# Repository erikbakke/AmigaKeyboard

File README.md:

# AmigaKeyboard
Replacement keyboard supporting MX-compatible switches, for all Amigas except A600 and A1200.

This keyboard design is based around an ATMega32U4 as keyboard controller, and is intended to be used as a replacement keyboards for Amigas with a keyboard controller on the keyboard.  This includes the A500, A1000, A2000, A3000 and A4000, including variants and towers.

The A600 and A1200 have the keyboard controller on the motherboard, and are not compatible with this keyboard design.

There are further notes in the Firmware and PCB folders, relevant to those parts of the project.

It should be noted that this is an early design, but I have built a keyboard up from scratch with this PCB and firmware and it is working on my A4000.
The design is not yet designed to fit into existing Amiga keyboard cases or as a 1:1 replacement for an A500 keyboard.  In order to achieve this, the mounting holes need to be adjusted to fit the external keyboard cases, and most likely a switch mounting plate will also be required.
To avoid disappointment, please keep this in mind before ordering PCBs from this design.

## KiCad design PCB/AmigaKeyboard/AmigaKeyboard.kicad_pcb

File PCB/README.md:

# AmigaKeyboard PCB files

This folder contains the schematics and PCB design for revision 0.2 of the Amiga replacement keyboard design as a KiCad project.  This was initially developed in KiCad 6, and is currently maintained in KiCad 7.

The keyboard works as is with my A4000, but I have not yet had a chance to test it with my A500.  The design should be electrically compatible, and I'm hoping it would be dimensionally compatible as well.
Some work will be required to fit the PCB to existing Amiga external keyboard housings.  The current design has mounting holes to fit a keyboard case I had lying around, so I would be very happy to receive positions and dimensions for mounting holes on the different Amiga keyboards for A2000, A3000 and A4000 models, and will update the design in any way I can to increase compatibility.

I am getting PCBs manufactured from time to time and still have some revision 0.1 PCBs left if anyone want one for experimenting.

## Change log
Revision 0.1:
- Initial PCB version for prototype board manufacture.
  
Revision 0.2:
- A missing trace between D180 and MX80 (numeric pad "4") has been fixed.  The bodge wire fix is no longer needed on revision 0.2.
- Added AVR ISP connector to assist in firmware upgrades and troubleshooting.

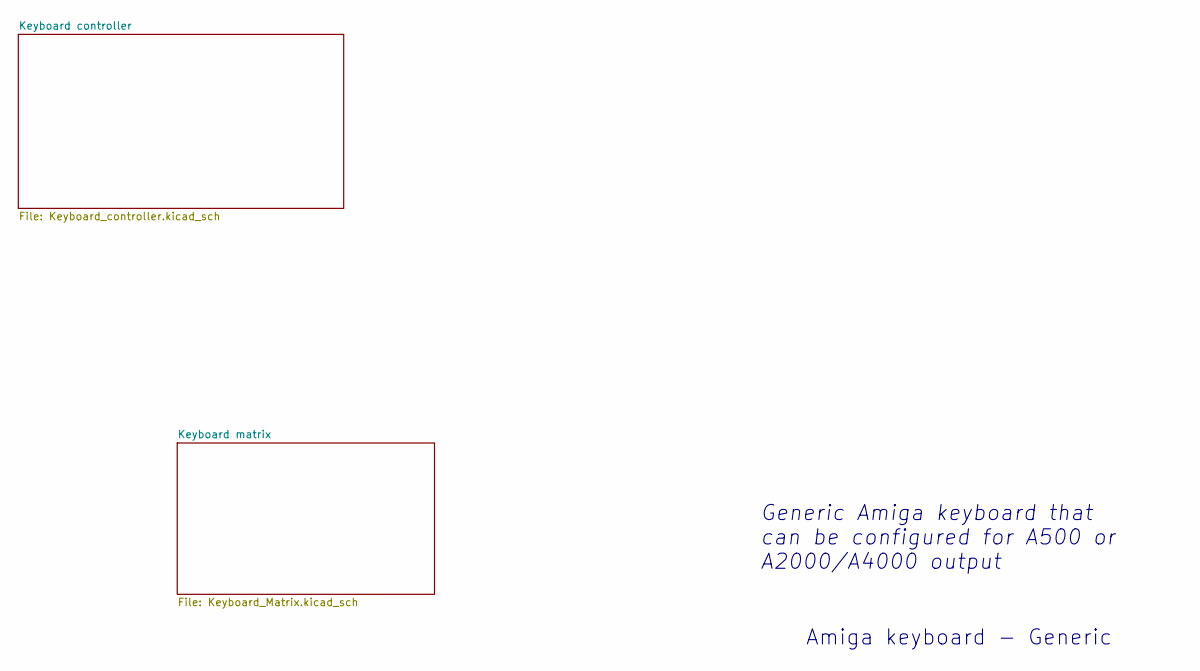
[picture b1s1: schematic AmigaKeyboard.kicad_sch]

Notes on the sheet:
Generic Amiga keyboard that can be configured for A500 or A2000/A4000 output
Amiga keyboard - Generic

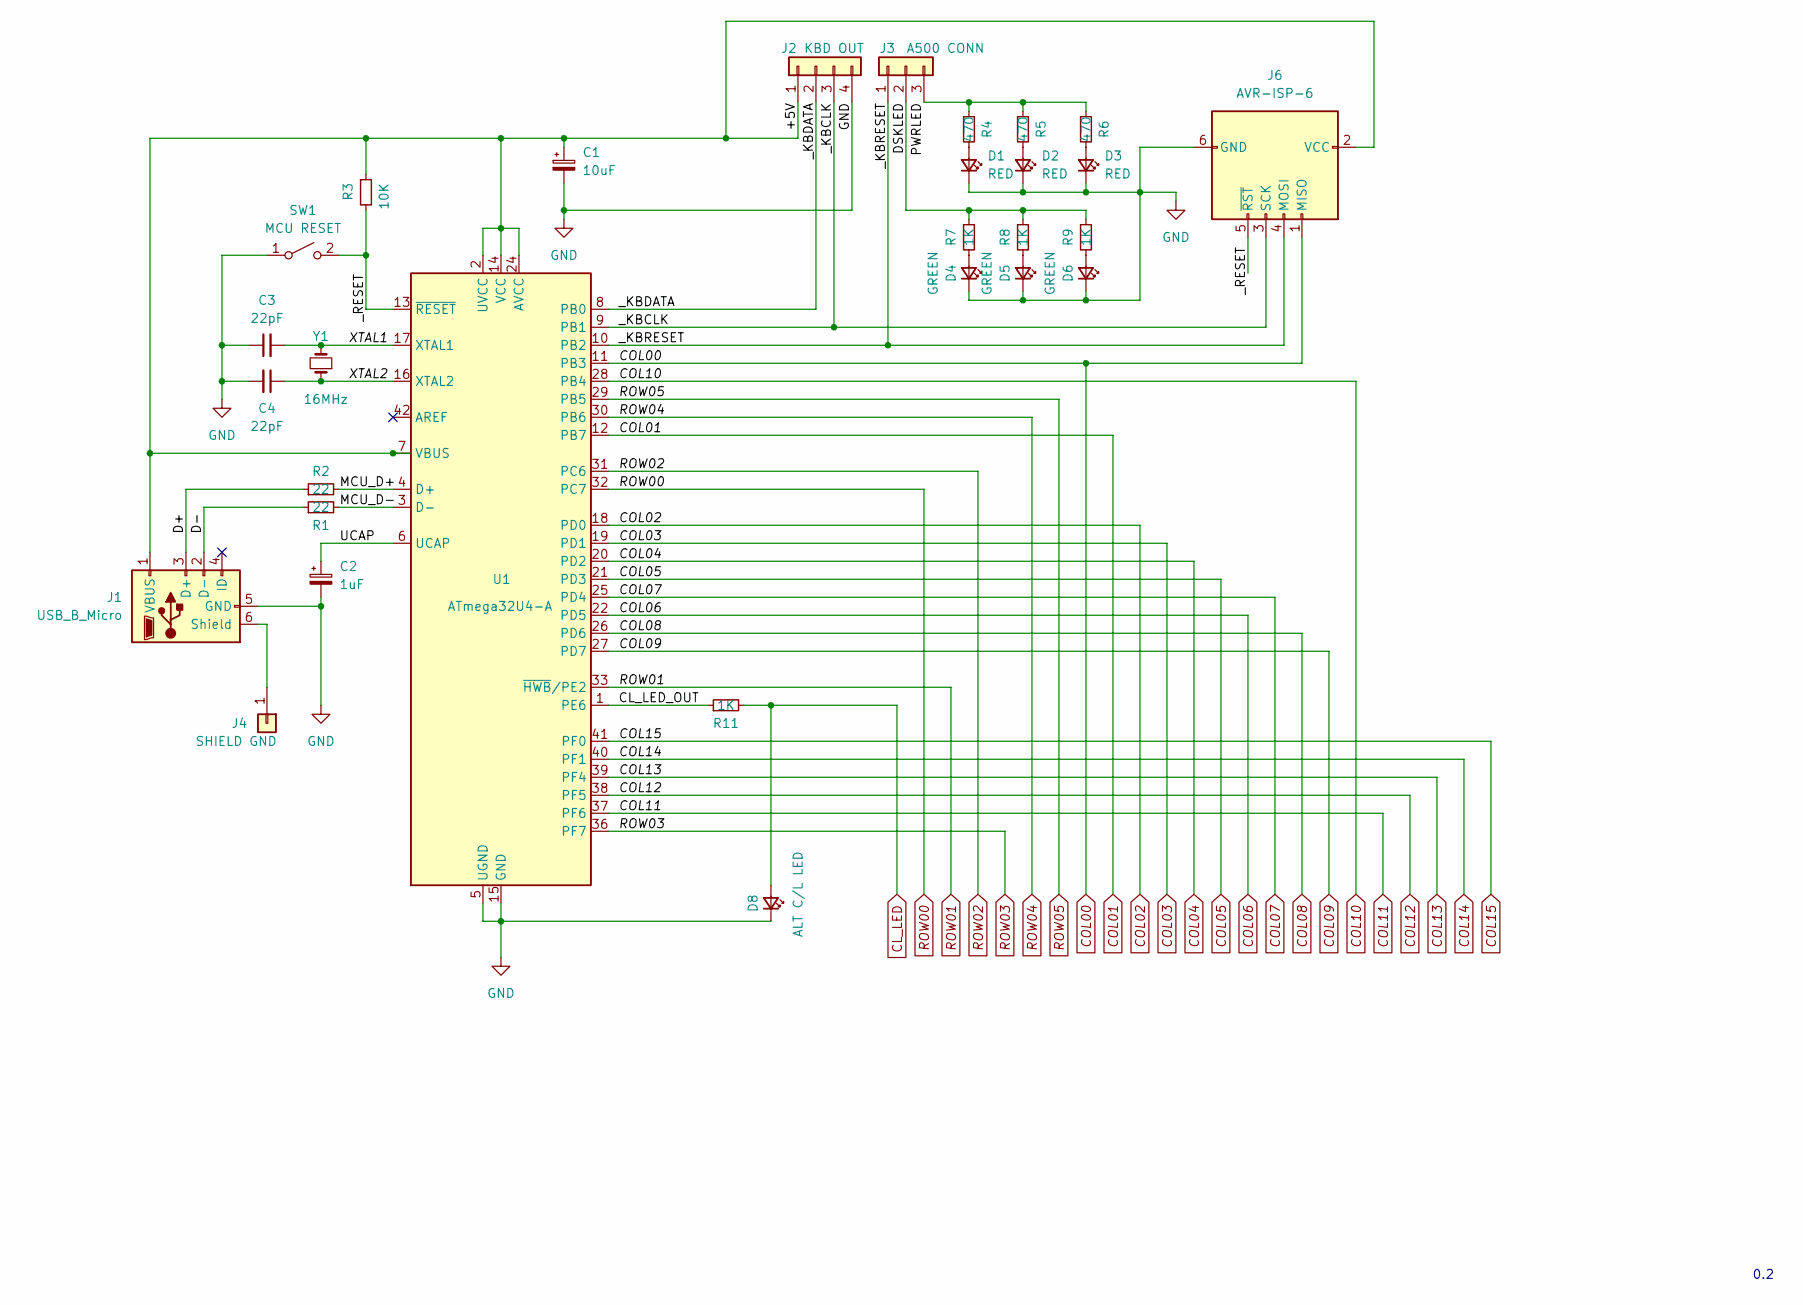
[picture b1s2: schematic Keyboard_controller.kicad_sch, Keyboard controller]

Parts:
C1: 10uF; CP_EIA-7343-31_Kemet-D
C2: 1uF; CP_EIA-3216-18_Kemet-A
C3, C4: 22pF; C_1206_3216Metric
D1, D2, D3: RED; LED_Rectangular_W5.0mm_H2.0mm
D4, D5, D6: GREEN; LED_Rectangular_W5.0mm_H2.0mm
D8: ALT C/L LED; LED_D3.0mm
J1: USB_B_Micro; USB_Micro-B_Wuerth_629105150521_CircularHoles
J2: KBD OUT; SolderWire-0.25sqmm_1x04_P4.2mm_D0.65mm_OD1.7mm
J3: A500 CONN; SolderWire-0.25sqmm_1x03_P4.2mm_D0.65mm_OD1.7mm
J4: SHIELD GND; SolderWire-2.5sqmm_1x01_D2.4mm_OD4.4mm
J6: AVR-ISP-6; PinHeader_2x03_P2.54mm_Vertical
R1, R2: 22; R_1206_3216Metric
R3: 10K; R_1206_3216Metric
R4, R5, R6: 470; R_1206_3216Metric
R7, R8, R9, R11: 1K; R_1206_3216Metric
SW1: MCU RESET; SW_PUSH_6mm
U1: ATmega32U4-A; TQFP-44_10x10mm_P0.8mm
Y1: 16MHz; Crystal_HC49-U_Vertical

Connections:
/Keyboard controller/+5V: C1.1, J1.1 (VBUS), J2.1, J6.2 (VCC), R3.1, U1.2 (UVCC), U1.7 (VBUS), U1.14 (VCC), U1.24 (AVCC), U1.34 (VCC), U1.44 (AVCC)
/Keyboard controller/CL_LED_OUT: R11.1, U1.1 (PE6)
/Keyboard controller/D+: J1.3 (D+), R2.1
/Keyboard controller/D-: J1.2 (D-), R1.1
/Keyboard controller/DSKLED: J3.2, R7.1, R8.1, R9.1
/Keyboard controller/MCU_D+: R2.2, U1.4 (D+)
/Keyboard controller/MCU_D-: R1.2, U1.3 (D-)
/Keyboard controller/PWRLED: J3.3, R4.1, R5.1, R6.1
/Keyboard controller/UCAP: C2.1, U1.6 (UCAP)
/Keyboard controller/XTAL1: C3.2, U1.17 (XTAL1), Y1.2
/Keyboard controller/XTAL2: C4.1, U1.16 (XTAL2), Y1.1
/Keyboard controller/_KBCLK: J2.3, J6.3 (SCK), U1.9 (PB1)
/Keyboard controller/_KBDATA: J2.2, U1.8 (PB0)
/Keyboard controller/_KBRESET: J3.1, J6.4 (MOSI), U1.10 (PB2)
/Keyboard controller/_RESET: J6.5 (~RST), R3.2, SW1.2 (B), U1.13 (~RESET)
CL_LED: D8.2 (A), R11.2; also elsewhere on the board
COL00: J6.1 (MISO), U1.11 (PB3); also elsewhere on the board
COL01: U1.12 (PB7); also elsewhere on the board
COL02: U1.18 (PD0); also elsewhere on the board
COL03: U1.19 (PD1); also elsewhere on the board
COL04: U1.20 (PD2); also elsewhere on the board
COL05: U1.21 (PD3); also elsewhere on the board
COL06: U1.22 (PD5); also elsewhere on the board
COL07: U1.25 (PD4); also elsewhere on the board
COL08: U1.26 (PD6); also elsewhere on the board
COL09: U1.27 (PD7); also elsewhere on the board
COL10: U1.28 (PB4); also elsewhere on the board
COL11: U1.37 (PF6); also elsewhere on the board
COL12: U1.38 (PF5); also elsewhere on the board
COL13: U1.39 (PF4); also elsewhere on the board
COL14: U1.40 (PF1); also elsewhere on the board
COL15: U1.41 (PF0); also elsewhere on the board
GND: C1.2, C2.2, C3.1, C4.2, D1.1 (K), D2.1 (K), D3.1 (K), D4.1 (K), D5.1 (K), D6.1 (K), D8.1 (K), J1.5 (GND), J2.4, J6.6 (GND), SW1.1 (A), U1.5 (UGND), U1.15 (GND), U1.23 (GND), U1.35 (GND), U1.43 (GND); also elsewhere on the board
unnamed: D1.2 (A), R4.2
unnamed: D2.2 (A), R5.2
unnamed: D3.2 (A), R6.2
unnamed: D4.2 (A), R7.2
unnamed: D5.2 (A), R8.2
unnamed: D6.2 (A), R9.2
unnamed: J1.6 (Shield), J4.1
ROW00: U1.32 (PC7); also elsewhere on the board
ROW01: U1.33 (~HWB/PE2); also elsewhere on the board
ROW02: U1.31 (PC6); also elsewhere on the board
ROW03: U1.36 (PF7); also elsewhere on the board
ROW04: U1.30 (PB6); also elsewhere on the board
ROW05: U1.29 (PB5); also elsewhere on the board

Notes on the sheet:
0.2

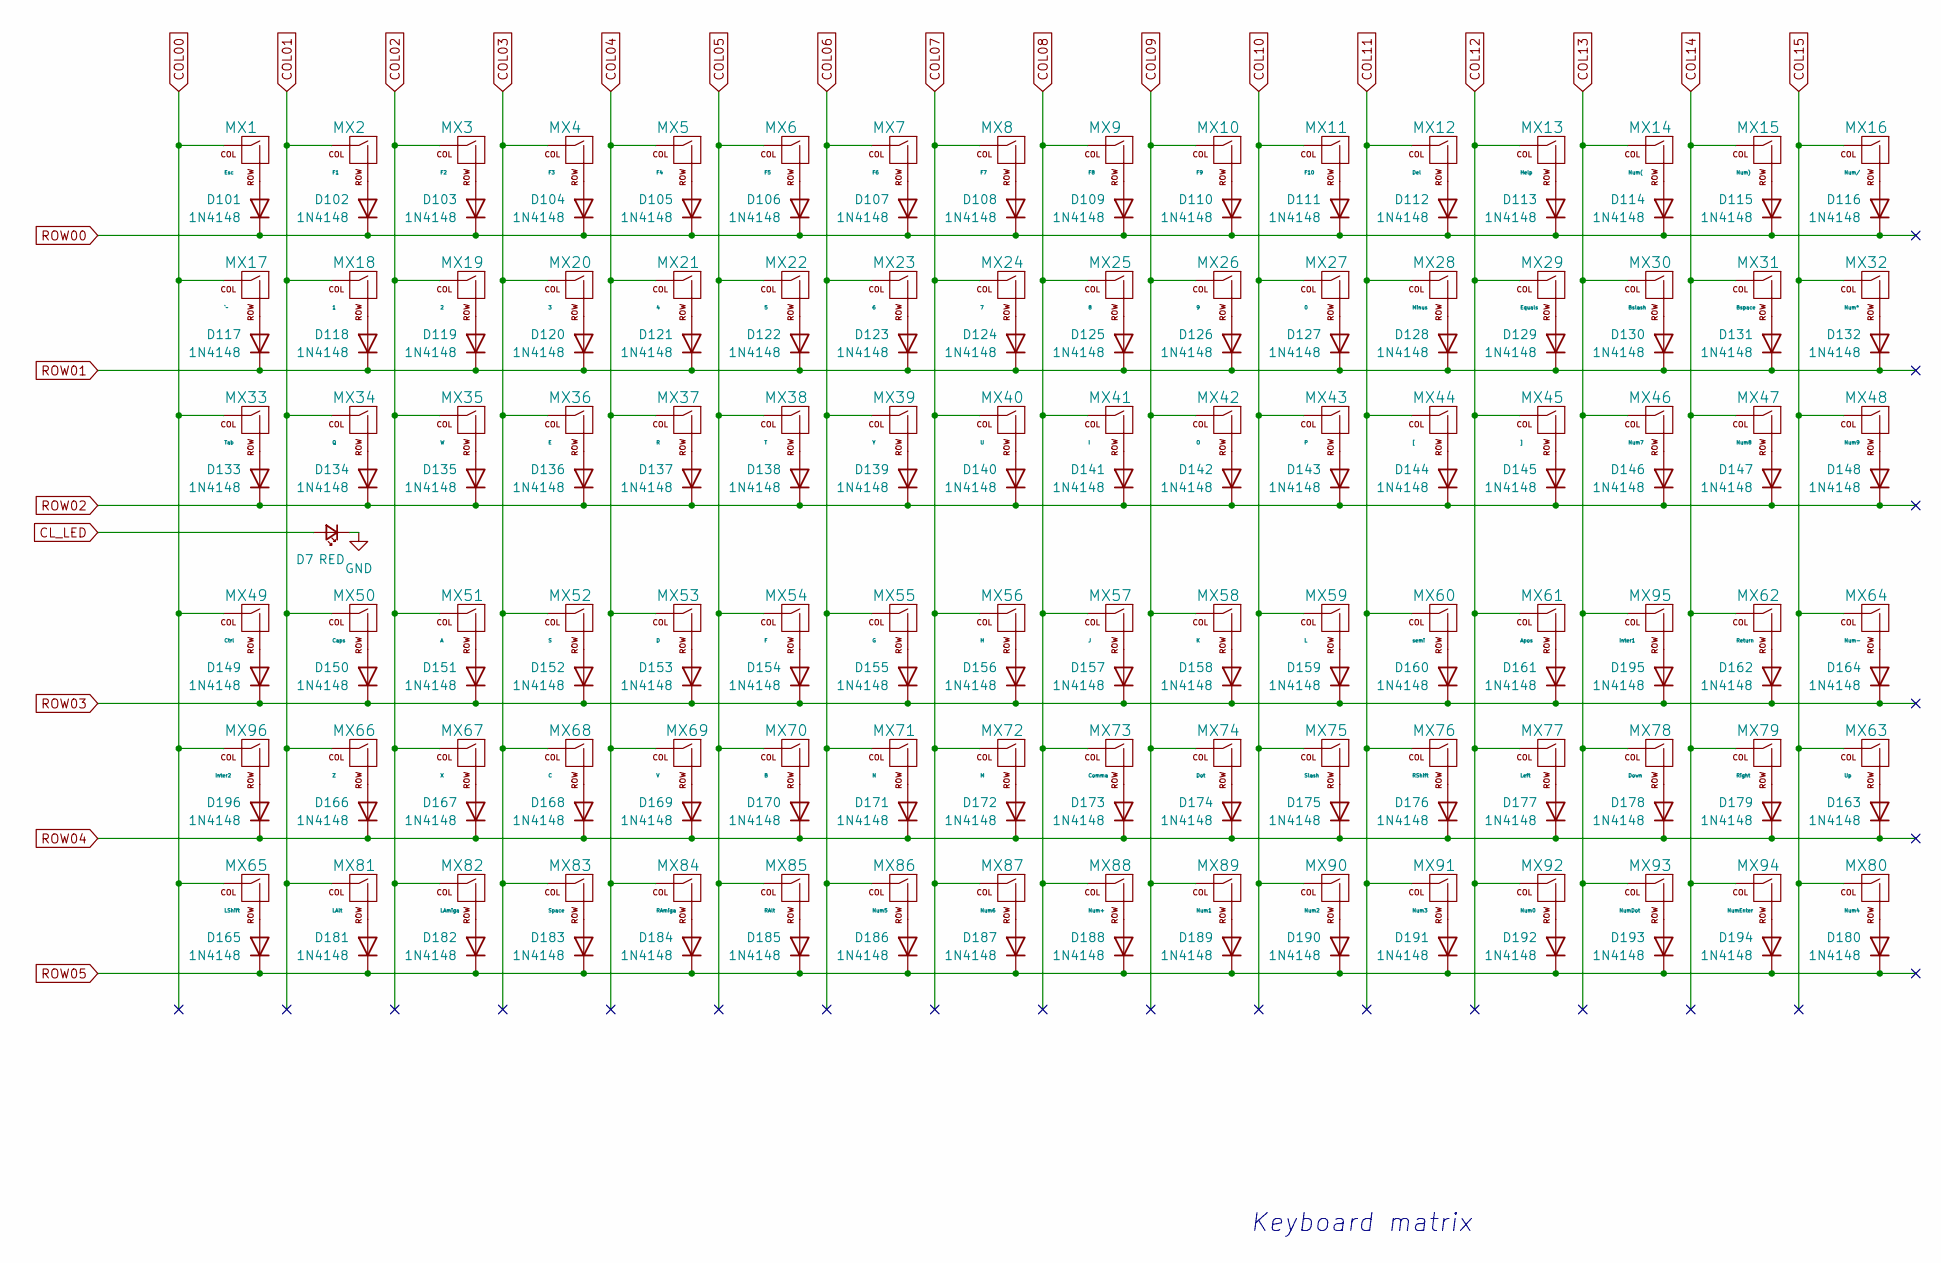
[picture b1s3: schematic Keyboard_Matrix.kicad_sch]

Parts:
D7: RED; LED_0805_2012Metric
D101, D102, D103, D104, D105, D106, D107, D108, D109, D110, D111, D112, D113, D114, D115, D116, D117, D118, D119, D120, D121, D122, D123, D124, D125, D126, D127, D128, D129, D130, D131, D132, D133, D134, D135, D136, D137, D138, D139, D140, D141, D142, D143, D144, D145, D146, D147, D148, D149, D150, D151, D152, D153, D154, D155, D156, D157, D158, D159, D160, D161, D162, D163, D164, D165, D166, D167, D168, D169, D170, D171, D172, D173, D174, D175, D176, D177, D178, D179, D180, D181, D182, D183, D184, D185, D186, D187, D188, D189, D190, D191, D192, D193, D194, D195, D196: 1N4148; D_0805_2012Metric_Pad1.15x1.40mm_HandSolder
MX1: Esc; SW_Cherry_MX_PCB_1.00u
MX2: F1; SW_Cherry_MX_PCB_1.25u
MX3: F2; SW_Cherry_MX_PCB_1.25u
MX4: F3; SW_Cherry_MX_PCB_1.25u
MX5: F4; SW_Cherry_MX_PCB_1.25u
MX6: F5; SW_Cherry_MX_PCB_1.25u
MX7: F6; SW_Cherry_MX_PCB_1.25u
MX8: F7; SW_Cherry_MX_PCB_1.25u
MX9: F8; SW_Cherry_MX_PCB_1.25u
MX10: F9; SW_Cherry_MX_PCB_1.25u
MX11: F10; SW_Cherry_MX_PCB_1.25u
MX12: Del; SW_Cherry_MX_PCB_1.50u
MX13: Help; SW_Cherry_MX_PCB_1.50u
MX14: Num(; SW_Cherry_MX_PCB_1.00u
MX15: Num); SW_Cherry_MX_PCB_1.00u
MX16: Num/; SW_Cherry_MX_PCB_1.00u
MX17: `~; SW_Cherry_MX_PCB_1.50u
MX18: 1; SW_Cherry_MX_PCB_1.00u
MX19: 2; SW_Cherry_MX_PCB_1.00u
MX20: 3; SW_Cherry_MX_PCB_1.00u
MX21: 4; SW_Cherry_MX_PCB_1.00u
MX22: 5; SW_Cherry_MX_PCB_1.00u
MX23: 6; SW_Cherry_MX_PCB_1.00u
MX24: 7; SW_Cherry_MX_PCB_1.00u
MX25: 8; SW_Cherry_MX_PCB_1.00u
MX26: 9; SW_Cherry_MX_PCB_1.00u
MX27: 0; SW_Cherry_MX_PCB_1.00u
MX28: Minus; SW_Cherry_MX_PCB_1.00u
MX29: Equals; SW_Cherry_MX_PCB_1.00u
MX30: Bslash; SW_Cherry_MX_PCB_1.00u
MX31: Bspace; SW_Cherry_MX_PCB_1.00u
MX32: Num*; SW_Cherry_MX_PCB_1.00u
MX33: Tab; SW_Cherry_MX_PCB_2.00u
MX34: Q; SW_Cherry_MX_PCB_1.00u
MX35: W; SW_Cherry_MX_PCB_1.00u
MX36: E; SW_Cherry_MX_PCB_1.00u
MX37: R; SW_Cherry_MX_PCB_1.00u
MX38: T; SW_Cherry_MX_PCB_1.00u
MX39: Y; SW_Cherry_MX_PCB_1.00u
MX40: U; SW_Cherry_MX_PCB_1.00u
MX41: I; SW_Cherry_MX_PCB_1.00u
MX42: O; SW_Cherry_MX_PCB_1.00u
MX43: P; SW_Cherry_MX_PCB_1.00u
MX44: [; SW_Cherry_MX_PCB_1.00u
MX45: ]; SW_Cherry_MX_PCB_1.00u
MX46: Num7; SW_Cherry_MX_PCB_1.00u
MX47: Num8; SW_Cherry_MX_PCB_1.00u
MX48: Num9; SW_Cherry_MX_PCB_1.00u
MX49: Ctrl; SW_Cherry_MX_PCB_1.25u
MX50: Caps; SW_Cherry_MX_PCB_1.00u
MX51: A; SW_Cherry_MX_PCB_1.00u
MX52: S; SW_Cherry_MX_PCB_1.00u
MX53: D; SW_Cherry_MX_PCB_1.00u
MX54: F; SW_Cherry_MX_PCB_1.00u
MX55: G; SW_Cherry_MX_PCB_1.00u
MX56: H; SW_Cherry_MX_PCB_1.00u
MX57: J; SW_Cherry_MX_PCB_1.00u
MX58: K; SW_Cherry_MX_PCB_1.00u
MX59: L; SW_Cherry_MX_PCB_1.00u
MX60: semi; SW_Cherry_MX_PCB_1.00u
MX61: Apos; SW_Cherry_MX_PCB_1.00u
MX62: Return; SW_Cherry_MX_PCB_ISOEnter
MX63: Up; SW_Cherry_MX_PCB_1.00u
MX64: Num-; SW_Cherry_MX_PCB_1.00u
MX65: LShift; SW_Cherry_MX_PCB_1.75u
MX66: Z; SW_Cherry_MX_PCB_1.00u
MX67: X; SW_Cherry_MX_PCB_1.00u
MX68: C; SW_Cherry_MX_PCB_1.00u
MX69: V; SW_Cherry_MX_PCB_1.00u
MX70: B; SW_Cherry_MX_PCB_1.00u
MX71: N; SW_Cherry_MX_PCB_1.00u
MX72: M; SW_Cherry_MX_PCB_1.00u
MX73: Comma; SW_Cherry_MX_PCB_1.00u
MX74: Dot; SW_Cherry_MX_PCB_1.00u
MX75: Slash; SW_Cherry_MX_PCB_1.00u
MX76: RShift; SW_Cherry_MX_PCB_2.50u
MX77: Left; SW_Cherry_MX_PCB_1.00u
MX78: Down; SW_Cherry_MX_PCB_1.00u
MX79: Right; SW_Cherry_MX_PCB_1.00u
MX80: Num4; SW_Cherry_MX_PCB_1.00u
MX81: LAlt; SW_Cherry_MX_PCB_1.25u
MX82: LAmiga; SW_Cherry_MX_PCB_1.25u
MX83: Space; SW_Cherry_MX_PCB_9.00u
MX84: RAmiga; SW_Cherry_MX_PCB_1.25u
MX85: RAlt; SW_Cherry_MX_PCB_1.25u
MX86: Num5; SW_Cherry_MX_PCB_1.00u
MX87: Num6; SW_Cherry_MX_PCB_1.00u
MX88: Num+; SW_Cherry_MX_PCB_1.00u
MX89: Num1; SW_Cherry_MX_PCB_1.00u
MX90: Num2; SW_Cherry_MX_PCB_1.00u
MX91: Num3; SW_Cherry_MX_PCB_1.00u
MX92: Num0; SW_Cherry_MX_PCB_2.00u
MX93: NumDot; SW_Cherry_MX_PCB_1.00u
MX94: NumEnter; SW_Cherry_MX_PCB_2.00u_90deg
MX95: Inter1; SW_Cherry_MX_PCB_1.00u
MX96: Inter2; SW_Cherry_MX_PCB_1.00u

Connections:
CL_LED: D7.2 (A); also elsewhere on the board
COL00: MX1.1 (COL), MX17.1 (COL), MX33.1 (COL), MX49.1 (COL), MX65.1 (COL), MX96.1 (COL); also elsewhere on the board
COL01: MX2.1 (COL), MX18.1 (COL), MX34.1 (COL), MX50.1 (COL), MX66.1 (COL), MX81.1 (COL); also elsewhere on the board
COL02: MX3.1 (COL), MX19.1 (COL), MX35.1 (COL), MX51.1 (COL), MX67.1 (COL), MX82.1 (COL); also elsewhere on the board
COL03: MX4.1 (COL), MX20.1 (COL), MX36.1 (COL), MX52.1 (COL), MX68.1 (COL), MX83.1 (COL); also elsewhere on the board
COL04: MX5.1 (COL), MX21.1 (COL), MX37.1 (COL), MX53.1 (COL), MX69.1 (COL), MX84.1 (COL); also elsewhere on the board
COL05: MX6.1 (COL), MX22.1 (COL), MX38.1 (COL), MX54.1 (COL), MX70.1 (COL), MX85.1 (COL); also elsewhere on the board
COL06: MX7.1 (COL), MX23.1 (COL), MX39.1 (COL), MX55.1 (COL), MX71.1 (COL), MX86.1 (COL); also elsewhere on the board
COL07: MX8.1 (COL), MX24.1 (COL), MX40.1 (COL), MX56.1 (COL), MX72.1 (COL), MX87.1 (COL); also elsewhere on the board
COL08: MX9.1 (COL), MX25.1 (COL), MX41.1 (COL), MX57.1 (COL), MX73.1 (COL), MX88.1 (COL); also elsewhere on the board
COL09: MX10.1 (COL), MX26.1 (COL), MX42.1 (COL), MX58.1 (COL), MX74.1 (COL), MX89.1 (COL); also elsewhere on the board
COL10: MX11.1 (COL), MX27.1 (COL), MX43.1 (COL), MX59.1 (COL), MX75.1 (COL), MX90.1 (COL); also elsewhere on the board
COL11: MX12.1 (COL), MX28.1 (COL), MX44.1 (COL), MX60.1 (COL), MX76.1 (COL), MX91.1 (COL); also elsewhere on the board
COL12: MX13.1 (COL), MX29.1 (COL), MX45.1 (COL), MX61.1 (COL), MX77.1 (COL), MX92.1 (COL); also elsewhere on the board
COL13: MX14.1 (COL), MX30.1 (COL), MX46.1 (COL), MX78.1 (COL), MX93.1 (COL), MX95.1 (COL); also elsewhere on the board
COL14: MX15.1 (COL), MX31.1 (COL), MX47.1 (COL), MX62.1 (COL), MX79.1 (COL), MX94.1 (COL); also elsewhere on the board
COL15: MX16.1 (COL), MX32.1 (COL), MX48.1 (COL), MX63.1 (COL), MX64.1 (COL), MX80.1 (COL); also elsewhere on the board
GND: D7.1 (K); also elsewhere on the board
unnamed: D101.2 (A), MX1.2 (ROW)
unnamed: D102.2 (A), MX2.2 (ROW)
unnamed: D103.2 (A), MX3.2 (ROW)
unnamed: D104.2 (A), MX4.2 (ROW)
unnamed: D105.2 (A), MX5.2 (ROW)
unnamed: D106.2 (A), MX6.2 (ROW)
unnamed: D107.2 (A), MX7.2 (ROW)
unnamed: D108.2 (A), MX8.2 (ROW)
unnamed: D109.2 (A), MX9.2 (ROW)
unnamed: D110.2 (A), MX10.2 (ROW)
unnamed: D111.2 (A), MX11.2 (ROW)
unnamed: D112.2 (A), MX12.2 (ROW)
unnamed: D113.2 (A), MX13.2 (ROW)
unnamed: D114.2 (A), MX14.2 (ROW)
unnamed: D115.2 (A), MX15.2 (ROW)
unnamed: D116.2 (A), MX16.2 (ROW)
unnamed: D117.2 (A), MX17.2 (ROW)
unnamed: D118.2 (A), MX18.2 (ROW)
unnamed: D119.2 (A), MX19.2 (ROW)
unnamed: D120.2 (A), MX20.2 (ROW)
unnamed: D121.2 (A), MX21.2 (ROW)
unnamed: D122.2 (A), MX22.2 (ROW)
unnamed: D123.2 (A), MX23.2 (ROW)
unnamed: D124.2 (A), MX24.2 (ROW)
unnamed: D125.2 (A), MX25.2 (ROW)
unnamed: D126.2 (A), MX26.2 (ROW)
unnamed: D127.2 (A), MX27.2 (ROW)
unnamed: D128.2 (A), MX28.2 (ROW)
unnamed: D129.2 (A), MX29.2 (ROW)
unnamed: D130.2 (A), MX30.2 (ROW)
unnamed: D131.2 (A), MX31.2 (ROW)
unnamed: D132.2 (A), MX32.2 (ROW)
unnamed: D133.2 (A), MX33.2 (ROW)
unnamed: D134.2 (A), MX34.2 (ROW)
unnamed: D135.2 (A), MX35.2 (ROW)
unnamed: D136.2 (A), MX36.2 (ROW)
unnamed: D137.2 (A), MX37.2 (ROW)
unnamed: D138.2 (A), MX38.2 (ROW)
unnamed: D139.2 (A), MX39.2 (ROW)
unnamed: D140.2 (A), MX40.2 (ROW)
unnamed: D141.2 (A), MX41.2 (ROW)
unnamed: D142.2 (A), MX42.2 (ROW)
unnamed: D143.2 (A), MX43.2 (ROW)
unnamed: D144.2 (A), MX44.2 (ROW)
unnamed: D145.2 (A), MX45.2 (ROW)
unnamed: D146.2 (A), MX46.2 (ROW)
unnamed: D147.2 (A), MX47.2 (ROW)
unnamed: D148.2 (A), MX48.2 (ROW)
unnamed: D149.2 (A), MX49.2 (ROW)
unnamed: D150.2 (A), MX50.2 (ROW)
unnamed: D151.2 (A), MX51.2 (ROW)
unnamed: D152.2 (A), MX52.2 (ROW)
unnamed: D153.2 (A), MX53.2 (ROW)
unnamed: D154.2 (A), MX54.2 (ROW)
unnamed: D155.2 (A), MX55.2 (ROW)
unnamed: D156.2 (A), MX56.2 (ROW)
unnamed: D157.2 (A), MX57.2 (ROW)
unnamed: D158.2 (A), MX58.2 (ROW)
unnamed: D159.2 (A), MX59.2 (ROW)
unnamed: D160.2 (A), MX60.2 (ROW)
unnamed: D161.2 (A), MX61.2 (ROW)
unnamed: D162.2 (A), MX62.2 (ROW)
unnamed: D163.2 (A), MX63.2 (ROW)
unnamed: D164.2 (A), MX64.2 (ROW)
unnamed: D165.2 (A), MX65.2 (ROW)
unnamed: D166.2 (A), MX66.2 (ROW)
unnamed: D167.2 (A), MX67.2 (ROW)
unnamed: D168.2 (A), MX68.2 (ROW)
unnamed: D169.2 (A), MX69.2 (ROW)
unnamed: D170.2 (A), MX70.2 (ROW)
unnamed: D171.2 (A), MX71.2 (ROW)
unnamed: D172.2 (A), MX72.2 (ROW)
unnamed: D173.2 (A), MX73.2 (ROW)
unnamed: D174.2 (A), MX74.2 (ROW)
unnamed: D175.2 (A), MX75.2 (ROW)
unnamed: D176.2 (A), MX76.2 (ROW)
unnamed: D177.2 (A), MX77.2 (ROW)
unnamed: D178.2 (A), MX78.2 (ROW)
unnamed: D179.2 (A), MX79.2 (ROW)
unnamed: D180.2 (A), MX80.2 (ROW)
unnamed: D181.2 (A), MX81.2 (ROW)
unnamed: D182.2 (A), MX82.2 (ROW)
unnamed: D183.2 (A), MX83.2 (ROW)
unnamed: D184.2 (A), MX84.2 (ROW)
unnamed: D185.2 (A), MX85.2 (ROW)
unnamed: D186.2 (A), MX86.2 (ROW)
unnamed: D187.2 (A), MX87.2 (ROW)
unnamed: D188.2 (A), MX88.2 (ROW)
unnamed: D189.2 (A), MX89.2 (ROW)
unnamed: D190.2 (A), MX90.2 (ROW)
unnamed: D191.2 (A), MX91.2 (ROW)
unnamed: D192.2 (A), MX92.2 (ROW)
unnamed: D193.2 (A), MX93.2 (ROW)
unnamed: D194.2 (A), MX94.2 (ROW)
unnamed: D195.2 (A), MX95.2 (ROW)
unnamed: D196.2 (A), MX96.2 (ROW)
ROW00: D101.1 (K), D102.1 (K), D103.1 (K), D104.1 (K), D105.1 (K), D106.1 (K), D107.1 (K), D108.1 (K), D109.1 (K), D110.1 (K), D111.1 (K), D112.1 (K), D113.1 (K), D114.1 (K), D115.1 (K), D116.1 (K); also elsewhere on the board
ROW01: D117.1 (K), D118.1 (K), D119.1 (K), D120.1 (K), D121.1 (K), D122.1 (K), D123.1 (K), D124.1 (K), D125.1 (K), D126.1 (K), D127.1 (K), D128.1 (K), D129.1 (K), D130.1 (K), D131.1 (K), D132.1 (K); also elsewhere on the board
ROW02: D133.1 (K), D134.1 (K), D135.1 (K), D136.1 (K), D137.1 (K), D138.1 (K), D139.1 (K), D140.1 (K), D141.1 (K), D142.1 (K), D143.1 (K), D144.1 (K), D145.1 (K), D146.1 (K), D147.1 (K), D148.1 (K); also elsewhere on the board
ROW03: D149.1 (K), D150.1 (K), D151.1 (K), D152.1 (K), D153.1 (K), D154.1 (K), D155.1 (K), D156.1 (K), D157.1 (K), D158.1 (K), D159.1 (K), D160.1 (K), D161.1 (K), D162.1 (K), D164.1 (K), D195.1 (K); also elsewhere on the board
ROW04: D163.1 (K), D166.1 (K), D167.1 (K), D168.1 (K), D169.1 (K), D170.1 (K), D171.1 (K), D172.1 (K), D173.1 (K), D174.1 (K), D175.1 (K), D176.1 (K), D177.1 (K), D178.1 (K), D179.1 (K), D196.1 (K); also elsewhere on the board
ROW05: D165.1 (K), D180.1 (K), D181.1 (K), D182.1 (K), D183.1 (K), D184.1 (K), D185.1 (K), D186.1 (K), D187.1 (K), D188.1 (K), D189.1 (K), D190.1 (K), D191.1 (K), D192.1 (K), D193.1 (K), D194.1 (K); also elsewhere on the board

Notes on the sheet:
Keyboard matrix

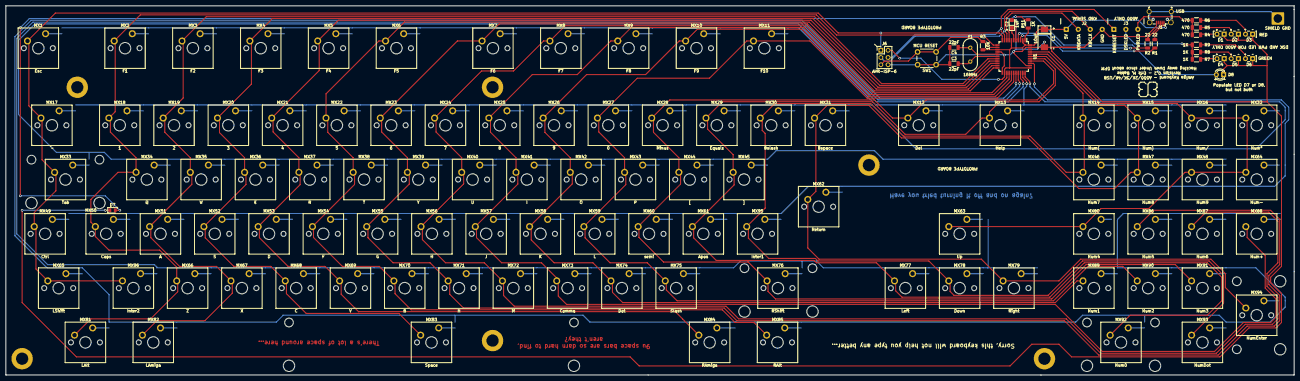
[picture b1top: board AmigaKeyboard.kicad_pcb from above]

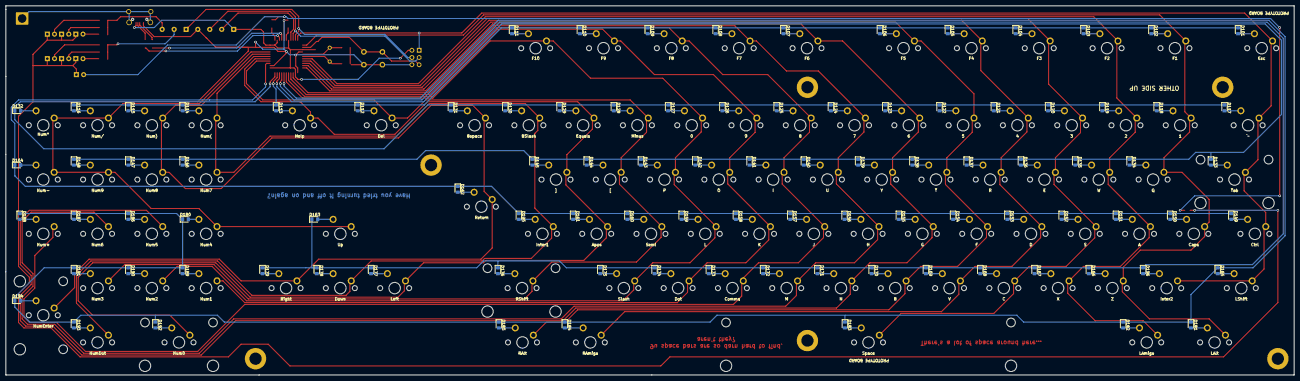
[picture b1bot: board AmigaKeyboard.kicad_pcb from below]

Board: 2 copper layers, 452.1 x 129.5 mm, 233 parts (96 on the bottom side), 142 nets.

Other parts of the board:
MNT01, MNT02, MNT03, MNT04, MNT05, MNT07: MountingHole_4.3mm_M4_DIN965_Pad
STAB01: Stabilizer_Cherry_MX_6.25u
STAB02, STAB02#2, STAB02#3, STAB02#4: Stabilizer_Cherry_MX_2.00u

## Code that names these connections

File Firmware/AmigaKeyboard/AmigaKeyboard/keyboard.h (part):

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#define KBDATA_OUT		( PORTB )
#define KBDATA_IN		( PINB )
#define KBDATA_DDR		( DDRB )
#define KBDATA_PIN		( 0 )
#define KBDATA_MASK		( 1 << KBDATA_PIN )

#define KBCLK_OUT		( PORTB )
#define KBCLK_DDR		( DDRB )
#define KBCLK_PIN		( 1 )
#define KBCLK_MASK		( 1 << KBCLK_PIN )

#define KBRESET_OUT		( PORTB )
#define KBRESET_DDR		( DDRB )
#define KBRESET_PIN		( 2 )
#define KBRESET_MASK	( 1 << KBRESET_PIN )

// Column signals
#define COL00_IN		( PINB )
#define COL00_DDR		( DDRB )
#define COL00_PIN		( 3 )
#define COL00_MASK		( 1 << COL00_PIN )

#define COL01_IN		( PINB )
#define COL01_DDR		( DDRB )
#define COL01_PIN		( 7 )
#define COL01_MASK		( 1 << COL01_PIN )

#define COL02_IN		( PIND )
#define COL02_DDR		( DDRD )
#define COL02_PIN		( 0 )
#define COL02_MASK		( 1 << COL02_PIN )

#define COL03_IN		( PIND )
#define COL03_DDR		( DDRD )
#define COL03_PIN		( 1 )
#define COL03_MASK		( 1 << COL03_PIN )

#define COL04_IN		( PIND )
#define COL04_DDR		( DDRD )
#define COL04_PIN		( 2 )
#define COL04_MASK		( 1 << COL04_PIN )

#define COL05_IN		( PIND )
#define COL05_DDR		( DDRD )
#define COL05_PIN		( 3 )
#define COL05_MASK		( 1 << COL05_PIN )

#define COL06_IN		( PIND )
#define COL06_DDR		( DDRD )
#define COL06_PIN		( 5 )
#define COL06_MASK		( 1 << COL06_PIN )

#define COL07_IN		( PIND )
#define COL07_DDR		( DDRD )
#define COL07_PIN		( 4 )
#define COL07_MASK		( 1 << COL07_PIN )

#define COL08_IN		( PIND )
#define COL08_DDR		( DDRD )
#define COL08_PIN		( 6 )
#define COL08_MASK		( 1 << COL08_PIN )

#define COL09_IN		( PIND )
#define COL09_DDR		( DDRD )
#define COL09_PIN		( 7 )
#define COL09_MASK		( 1 << COL09_PIN )

#define COL10_IN		( PINB )
#define COL10_DDR		( DDRB )
#define COL10_PIN		( 4 )
#define COL10_MASK		( 1 << COL10_PIN )

#define COL11_IN		( PINF )
#define COL11_DDR		( DDRF )
#define COL11_PIN		( 6 )
#define COL11_MASK		( 1 << COL11_PIN )

#define COL12_IN		( PINF )
#define COL12_DDR		( DDRF )
#define COL12_PIN		( 5 )
#define COL12_MASK		( 1 << COL12_PIN )

#define COL13_IN		( PINF )
#define COL13_DDR		( DDRF )
#define COL13_PIN		( 4 )
#define COL13_MASK		( 1 << COL13_PIN )

#define COL14_IN		( PINF )
#define COL14_DDR		( DDRF )
#define COL14_PIN		( 1 )
#define COL14_MASK		( 1 << COL14_PIN )

#define COL15_IN		( PINF )
#define COL15_DDR		( DDRF )
#define COL15_PIN		( 0 )
#define COL15_MASK		( 1 << COL15_PIN )

// Row signals
#define ROW00_OUT		( PORTC )
#define ROW00_DDR		( DDRC )
#define ROW00_PIN		( 7 )
#define ROW00_MASK		( 1 << ROW00_PIN )

#define ROW01_OUT		( PORTE )
#define ROW01_DDR		( DDRE )
#define ROW01_PIN		( 2 )
#define ROW01_MASK		( 1 << ROW01_PIN )

#define ROW02_OUT		( PORTC )
#define ROW02_DDR		( DDRC )
#define ROW02_PIN		( 6 )
#define ROW02_MASK		( 1 << ROW02_PIN )

#define ROW03_OUT		( PORTF )
#define ROW03_DDR		( DDRF )
#define ROW03_PIN		( 7 )
#define ROW03_MASK		( 1 << ROW03_PIN )

#define ROW04_OUT		( PORTB )
#define ROW04_DDR		( DDRB )
#define ROW04_PIN		( 6 )
#define ROW04_MASK		( 1 << ROW04_PIN )

#define ROW05_OUT		( PORTB )
#define ROW05_DDR		( DDRB )
#define ROW05_PIN		( 5 )
#define ROW05_MASK		( 1 << ROW05_PIN )

// Caps Lock
#define CAPS_OUT		( PORTE )
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
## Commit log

2024-05-05 Adding working copy of firmware sources
2024-05-05 Adding current PCB design and schematics
2024-05-05 Move README.me up one level
2024-05-05 Add 3D models folder
